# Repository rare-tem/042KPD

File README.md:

This is a 4x3 USB keypad using the STM32F042F6.

Please check the photos in the "img" folder.

To switch modes, press the Mode/DFU button.

The following is the key map in Mode 1 (the leftmost LED lights up).
    Ins    Home   PgUp
    Del    End    PgDn
    Lctrl  ↑      Lshift
    ←      ↓      →

The following is the key map in Mode 2 (the second LED from the left lights up).
    7&     8*     9(
    4$     5%     6^
    1!     2@     3#
    BkSp   0)     Enter

The following is the key map in Mode 3 (the 3rd LED from the left lights up).
    F10    F11    F12
    F7     F8     F9
    F4     F5     F6
    F1     F2     F3

The rightmost LED toggles whenever it receives USB SOF. (500Hz)

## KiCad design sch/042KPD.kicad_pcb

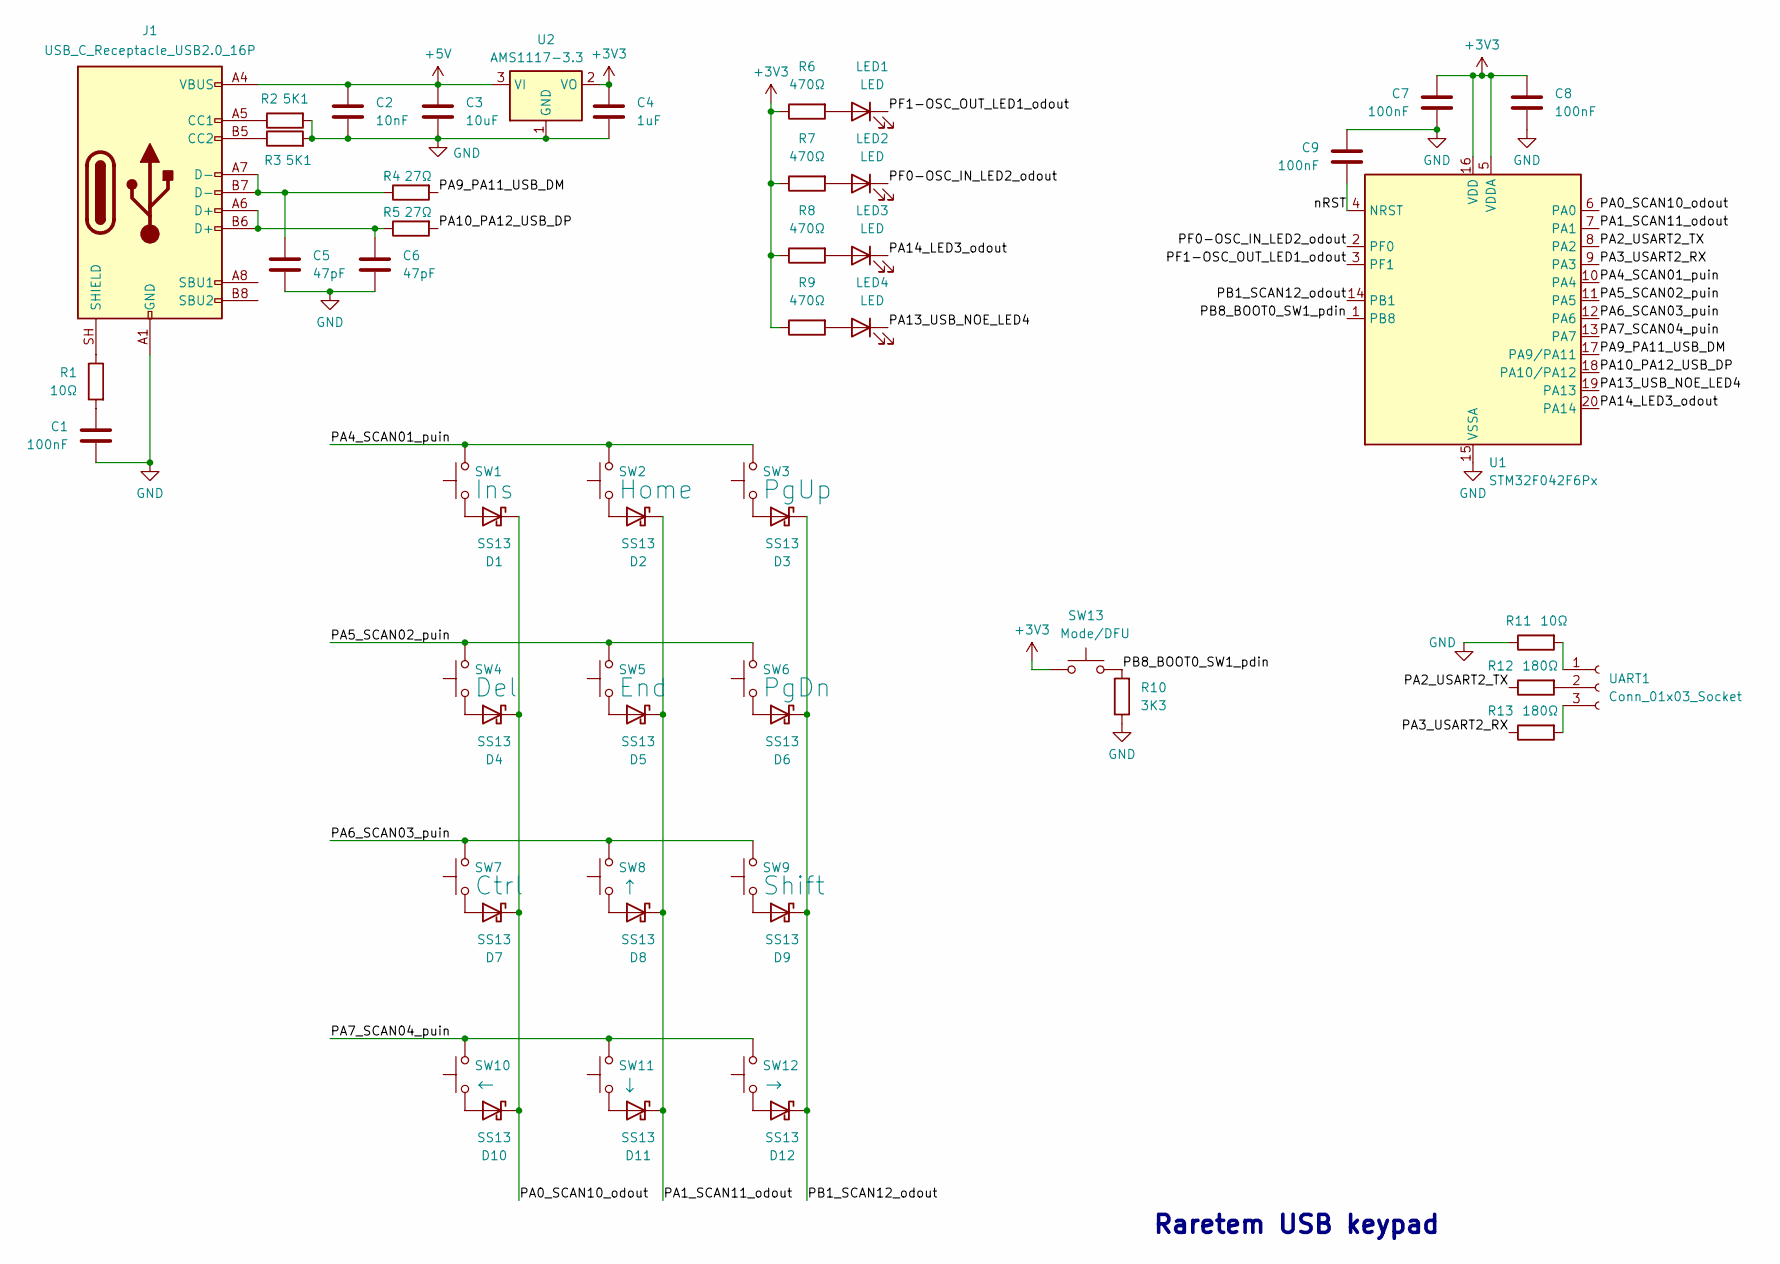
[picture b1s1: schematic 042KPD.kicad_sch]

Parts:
C1, C7, C8, C9: 100nF; C_0603_1608Metric_Pad1.08x0.95mm_HandSolder
C2: 10nF; C_0603_1608Metric_Pad1.08x0.95mm_HandSolder
C3: 10uF; C_0805_2012Metric_Pad1.18x1.45mm_HandSolder
C4: 1uF; C_0603_1608Metric_Pad1.08x0.95mm_HandSolder
C5, C6: 47pF; C_0603_1608Metric_Pad1.08x0.95mm_HandSolder
D1, D2, D3, D4, D5, D6, D7, D8, D9, D10, D11, D12: SS13; D_SS13
J1: USB_C_Receptacle_USB2.0_16P; USB_C_Receptacle_HH 16P TYPE-C (Y385)
LED1, LED2, LED3, LED4: LED; LED_0603_1608Metric_Pad1.05x0.95mm_HandSolder
R1, R11: 10Ω; R_0805_2012Metric_Pad1.20x1.40mm_HandSolder
R2, R3: 5K1; R_0603_1608Metric_Pad0.98x0.95mm_HandSolder
R4, R5: 27Ω; R_0603_1608Metric_Pad0.98x0.95mm_HandSolder
R6, R7, R8, R9: 470Ω; R_0603_1608Metric_Pad0.98x0.95mm_HandSolder
R10: 3K3; R_0603_1608Metric_Pad0.98x0.95mm_HandSolder
R12, R13: 180Ω; R_0603_1608Metric_Pad0.98x0.95mm_HandSolder
SW1: Ins; SW_CherryMX_PCB
SW2: Home; SW_CherryMX_PCB
SW3: PgUp; SW_CherryMX_PCB
SW4: Del; SW_CherryMX_PCB
SW5: End; SW_CherryMX_PCB
SW6: PgDn; SW_CherryMX_PCB
SW7: Ctrl; SW_CherryMX_PCB
SW8: ↑; SW_CherryMX_PCB
SW9: Shift; SW_CherryMX_PCB
SW10: ←; SW_CherryMX_PCB
SW11: ↓; SW_CherryMX_PCB
SW12: →; SW_CherryMX_PCB
SW13: Mode/DFU; SW_Tactile_SPST_6.1x1.2
U1: STM32F042F6Px; TSSOP-20_4.4x6.5mm_P0.65mm
U2: AMS1117-3.3; SOT-89-3_Handsoldering
UART1: Conn_01x03_Socket; PinHeader-03_P2.54mm

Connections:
+3V3: C4.1, C7.1, C8.1, R6.1, R7.1, R8.1, R9.1, SW13.1, U1.5 (VDDA), U1.16 (VDD), U2.2 (VO)
+5V: C2.1, C3.1, J1.A4 (VBUS), J1.A9 (VBUS), J1.B4 (VBUS), J1.B9 (VBUS), U2.3 (VI)
/PA0_SCAN10_odout: D1.1 (K), D4.1 (K), D7.1 (K), D10.1 (K), U1.6 (PA0)
/PA1_SCAN11_odout: D2.1 (K), D5.1 (K), D8.1 (K), D11.1 (K), U1.7 (PA1)
/PA2_USART2_TX: R12.1, U1.8 (PA2)
/PA3_USART2_RX: R13.1, U1.9 (PA3)
/PA4_SCAN01_puin: SW1.2, SW2.2, SW3.2, U1.10 (PA4)
/PA5_SCAN02_puin: SW4.2, SW5.2, SW6.2, U1.11 (PA5)
/PA6_SCAN03_puin: SW7.2, SW8.2, SW9.2, U1.12 (PA6)
/PA7_SCAN04_puin: SW10.2, SW11.2, SW12.2, U1.13 (PA7)
/PA9_PA11_USB_DM: R4.2, U1.17 (PA9/PA11)
/PA10_PA12_USB_DP: R5.2, U1.18 (PA10/PA12)
/PA13_USB_NOE_LED4: LED4.1 (K), U1.19 (PA13)
/PA14_LED3_odout: LED3.1 (K), U1.20 (PA14)
/PB1_SCAN12_odout: D3.1 (K), D6.1 (K), D9.1 (K), D12.1 (K), U1.14 (PB1)
/PB8_BOOT0_SW1_pdin: R10.2, SW13.2, U1.1 (PB8)
/PF0-OSC_IN_LED2_odout: LED2.1 (K), U1.2 (PF0)
/PF1-OSC_OUT_LED1_odout: LED1.1 (K), U1.3 (PF1)
/nRST: C9.1, U1.4 (NRST)
GND: C1.2, C2.2, C3.2, C4.2, C5.2, C6.2, C7.2, C8.2, C9.2, J1.A1 (GND), J1.A12 (GND), J1.B1 (GND), J1.B12 (GND), R2.2, R3.2, R10.1, R11.1, U1.15 (VSSA), U2.1 (GND)
unnamed: C1.1, R1.2
unnamed: C5.1, J1.A7 (D-), J1.B7 (D-), R4.1
unnamed: C6.1, J1.A6 (D+), J1.B6 (D+), R5.1
unnamed: D1.2 (A), SW1.1
unnamed: D2.2 (A), SW2.1
unnamed: D3.2 (A), SW3.1
unnamed: D4.2 (A), SW4.1
unnamed: D5.2 (A), SW5.1
unnamed: D6.2 (A), SW6.1
unnamed: D7.2 (A), SW7.1
unnamed: D8.2 (A), SW8.1
unnamed: D9.2 (A), SW9.1
unnamed: D10.2 (A), SW10.1
unnamed: D11.2 (A), SW11.1
unnamed: D12.2 (A), SW12.1
unnamed: J1.A5 (CC1), R2.1
unnamed: J1.B5 (CC2), R3.1
unnamed: J1.SH (SHIELD), R1.1
unnamed: LED1.2 (A), R6.2
unnamed: LED2.2 (A), R7.2
unnamed: LED3.2 (A), R8.2
unnamed: LED4.2 (A), R9.2
unnamed 42: R11.2, UART1.1; also elsewhere on the board
unnamed 43: R12.2, UART1.2; also elsewhere on the board
unnamed 44: R13.2, UART1.3; also elsewhere on the board

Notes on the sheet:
Raretem USB keypad

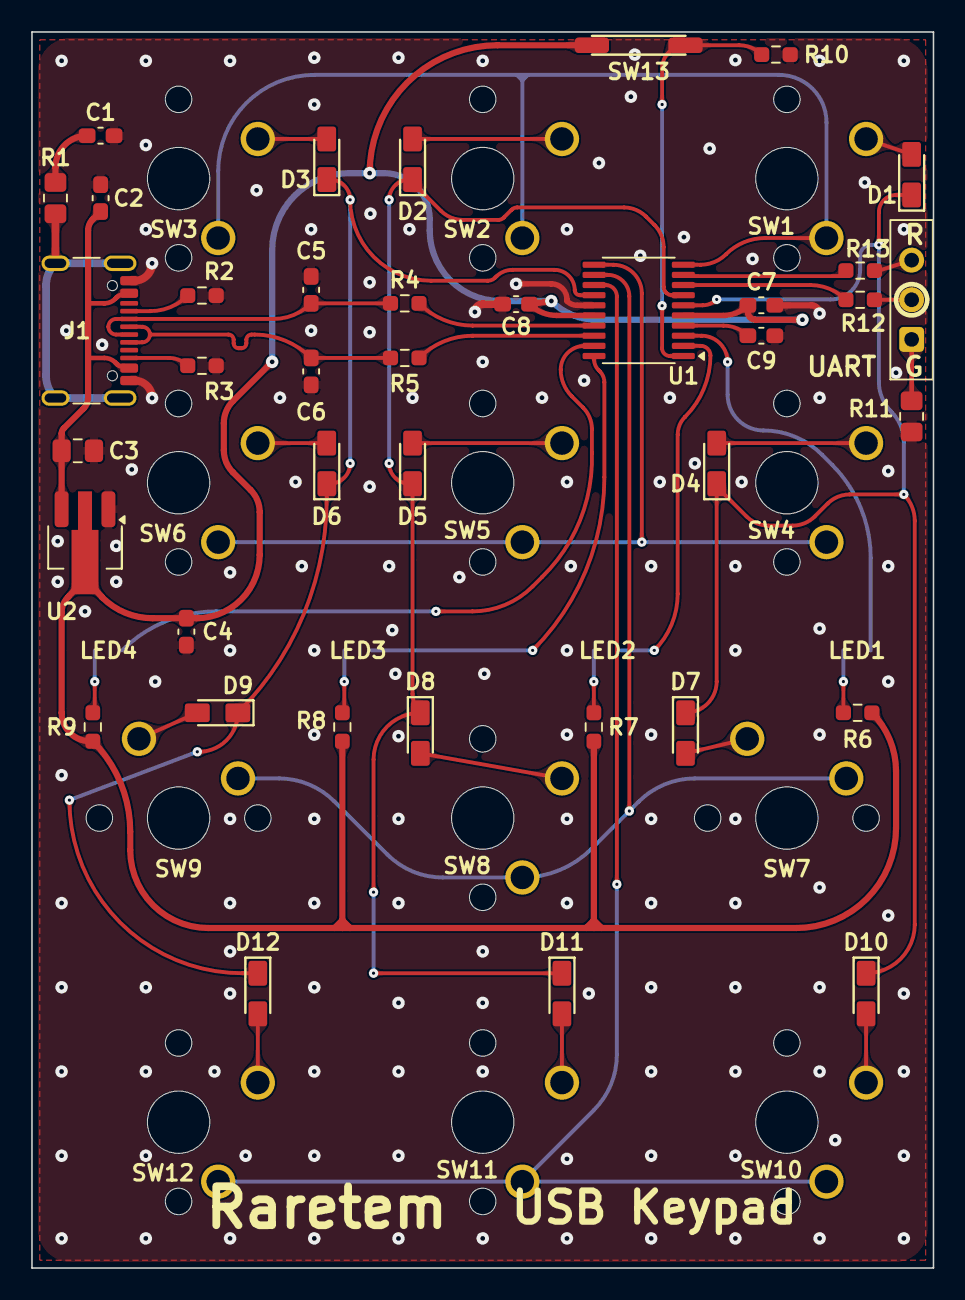
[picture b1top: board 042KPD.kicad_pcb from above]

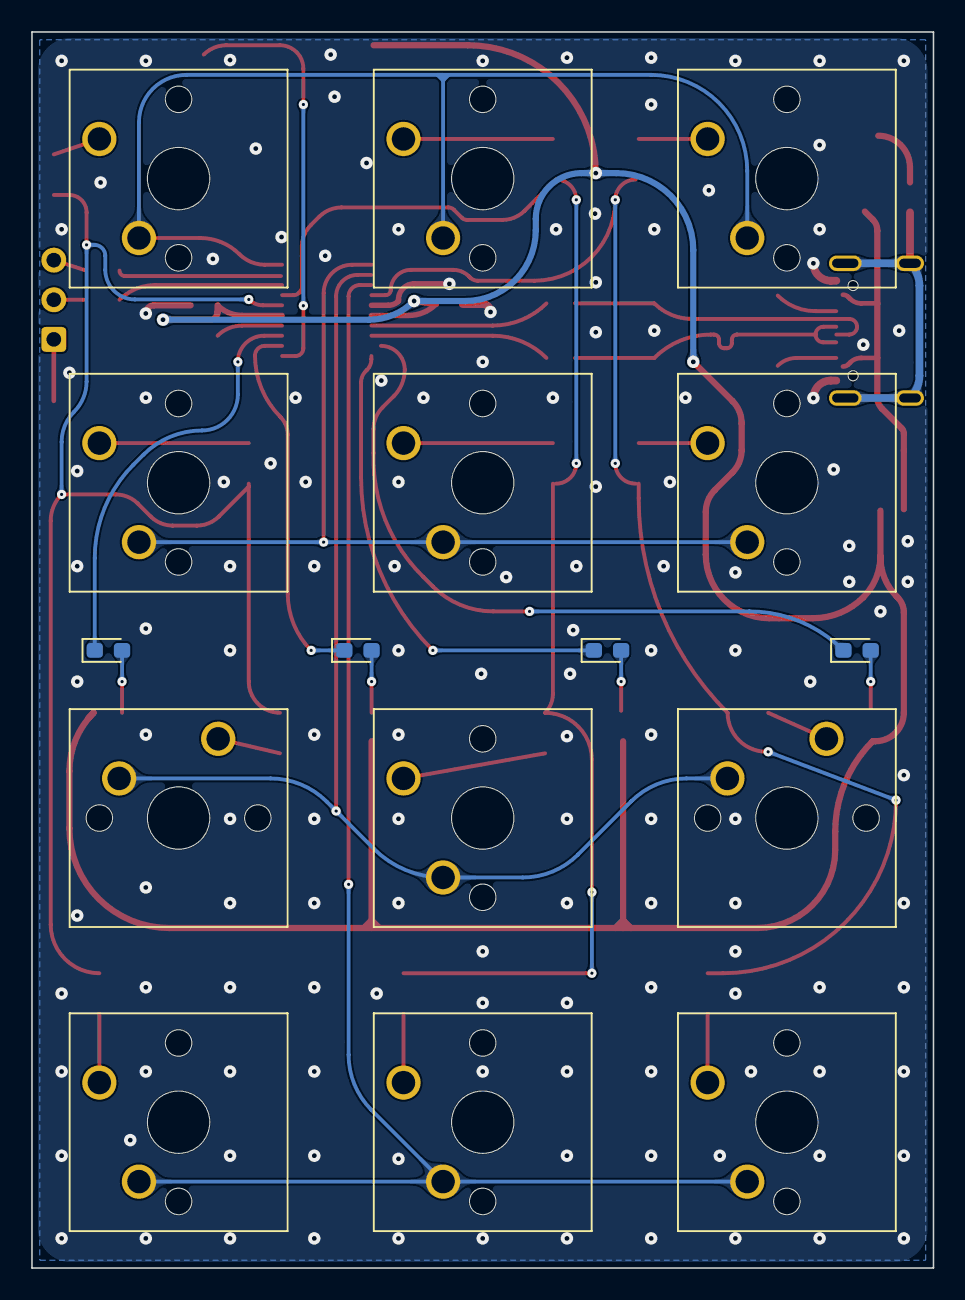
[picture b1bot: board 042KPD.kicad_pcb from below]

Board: 2 copper layers, 57.8 x 79.2 mm, 55 parts (16 on the bottom side), 45 nets.

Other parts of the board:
UART  G: Conn_01x03_Socket; PinHeader-03_P2.54mm

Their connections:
unnamed 42: UART G.1; also elsewhere on the board
unnamed 43: UART G.2; also elsewhere on the board
unnamed 44: UART G.3; also elsewhere on the board

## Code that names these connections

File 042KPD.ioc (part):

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Mcu.Name=STM32F042F6Px
Mcu.Package=TSSOP20
Mcu.UserName=STM32F042F6Px
PA0.GPIOParameters=GPIO_Speed,PinState,GPIO_PuPd,GPIO_Label,GPIO_ModeDefaultOutputPP
PA0.GPIO_Label=PA0_SCAN10_odout
PA0.GPIO_ModeDefaultOutputPP=GPIO_MODE_OUTPUT_OD
PA0.GPIO_PuPd=GPIO_PULLUP
PA0.GPIO_Speed=GPIO_SPEED_FREQ_LOW
PA0.PinState=GPIO_PIN_RESET
PA0.Signal=GPIO_Output
PA1.GPIOParameters=GPIO_Speed,PinState,GPIO_PuPd,GPIO_Label,GPIO_ModeDefaultOutputPP
PA1.GPIO_Label=PA1_SCAN11_odout
PA1.GPIO_ModeDefaultOutputPP=GPIO_MODE_OUTPUT_OD
PA1.GPIO_PuPd=GPIO_PULLUP
PA1.GPIO_Speed=GPIO_SPEED_FREQ_LOW
PA1.PinState=GPIO_PIN_SET
PA1.Signal=GPIO_Output
PA11.GPIOParameters=GPIO_Label
PA11.GPIO_Label=PA9_PA11_USB_DM
PA11.Mode=Device
PA11.Signal=USB_DM
PA12.GPIOParameters=GPIO_Label
PA12.GPIO_Label=PA10_PA12_USB_DP
PA12.Mode=Device
PA12.Signal=USB_DP
PA13.GPIOParameters=GPIO_PuPd,GPIO_Label,GPIO_ModeDefaultOutputPP
PA13.GPIO_Label=PA13_LED4_odout
PA13.GPIO_ModeDefaultOutputPP=GPIO_MODE_OUTPUT_OD
PA13.GPIO_PuPd=GPIO_NOPULL
PA13.Signal=GPIO_Output
PA14.GPIOParameters=GPIO_PuPd,GPIO_Label,GPIO_ModeDefaultOutputPP
PA14.GPIO_Label=PA14_LED3_odout
PA14.GPIO_ModeDefaultOutputPP=GPIO_MODE_OUTPUT_OD
PA14.GPIO_PuPd=GPIO_NOPULL
PA14.Signal=GPIO_Output
PA2.GPIOParameters=GPIO_Label
PA2.GPIO_Label=PA2_USART2_TX
PA2.Mode=Asynchronous
PA2.Signal=USART2_TX
PA3.GPIOParameters=GPIO_PuPd,GPIO_Label
PA3.GPIO_Label=PA3_USART2_RX
PA3.GPIO_PuPd=GPIO_PULLUP
PA3.Mode=Asynchronous
PA3.Signal=USART2_RX
PA4.GPIOParameters=GPIO_PuPd,GPIO_Label
PA4.GPIO_Label=PA4_SCAN01_puin
PA4.GPIO_PuPd=GPIO_PULLUP
PA4.Signal=GPIO_Input
PA5.GPIOParameters=GPIO_PuPd,GPIO_Label
PA5.GPIO_Label=PA5_SCAN02_puin
PA5.GPIO_PuPd=GPIO_PULLUP
PA5.Signal=GPIO_Input
PA6.GPIOParameters=GPIO_PuPd,GPIO_Label
PA6.GPIO_Label=PA6_SCAN03_puin
PA6.GPIO_PuPd=GPIO_PULLUP
PA6.Signal=GPIO_Input
PA7.GPIOParameters=GPIO_PuPd,GPIO_Label
PA7.GPIO_Label=PA7_SCAN04_puin
PA7.GPIO_PuPd=GPIO_PULLUP
PA7.Signal=GPIO_Input
PB1.GPIOParameters=PinState,GPIO_PuPd,GPIO_Label,GPIO_ModeDefaultOutputPP
PB1.GPIO_Label=PB1_SCAN12_odout
PB1.GPIO_ModeDefaultOutputPP=GPIO_MODE_OUTPUT_OD
PB1.GPIO_PuPd=GPIO_PULLUP
PB1.PinState=GPIO_PIN_SET
PB1.Signal=GPIO_Output
PB8.GPIOParameters=GPIO_PuPd,GPIO_Label
PB8.GPIO_Label=PB8_BOOT0_SW1_pdin
PB8.GPIO_PuPd=GPIO_PULLDOWN
PB8.Signal=GPIO_Input
PF0-OSC_IN.GPIOParameters=GPIO_PuPd,GPIO_Label,GPIO_ModeDefaultOutputPP
PF0-OSC_IN.GPIO_Label=PF0-OSC_IN_LED2_odout
PF0-OSC_IN.GPIO_ModeDefaultOutputPP=GPIO_MODE_OUTPUT_OD
PF0-OSC_IN.GPIO_PuPd=GPIO_NOPULL
PF0-OSC_IN.Signal=GPIO_Output
PF1-OSC_OUT.GPIOParameters=GPIO_PuPd,GPIO_Label,GPIO_ModeDefaultOutputPP
PF1-OSC_OUT.GPIO_Label=PF1-OSC_OUT_LED1_odout
PF1-OSC_OUT.GPIO_ModeDefaultOutputPP=GPIO_MODE_OUTPUT_OD
PF1-OSC_OUT.GPIO_PuPd=GPIO_NOPULL
PF1-OSC_OUT.Signal=GPIO_Output
RCC.SYSCLKFreq_VALUE=48000000
RCC.SYSCLKSource=RCC_SYSCLKSOURCE_HSI48
board=custom
